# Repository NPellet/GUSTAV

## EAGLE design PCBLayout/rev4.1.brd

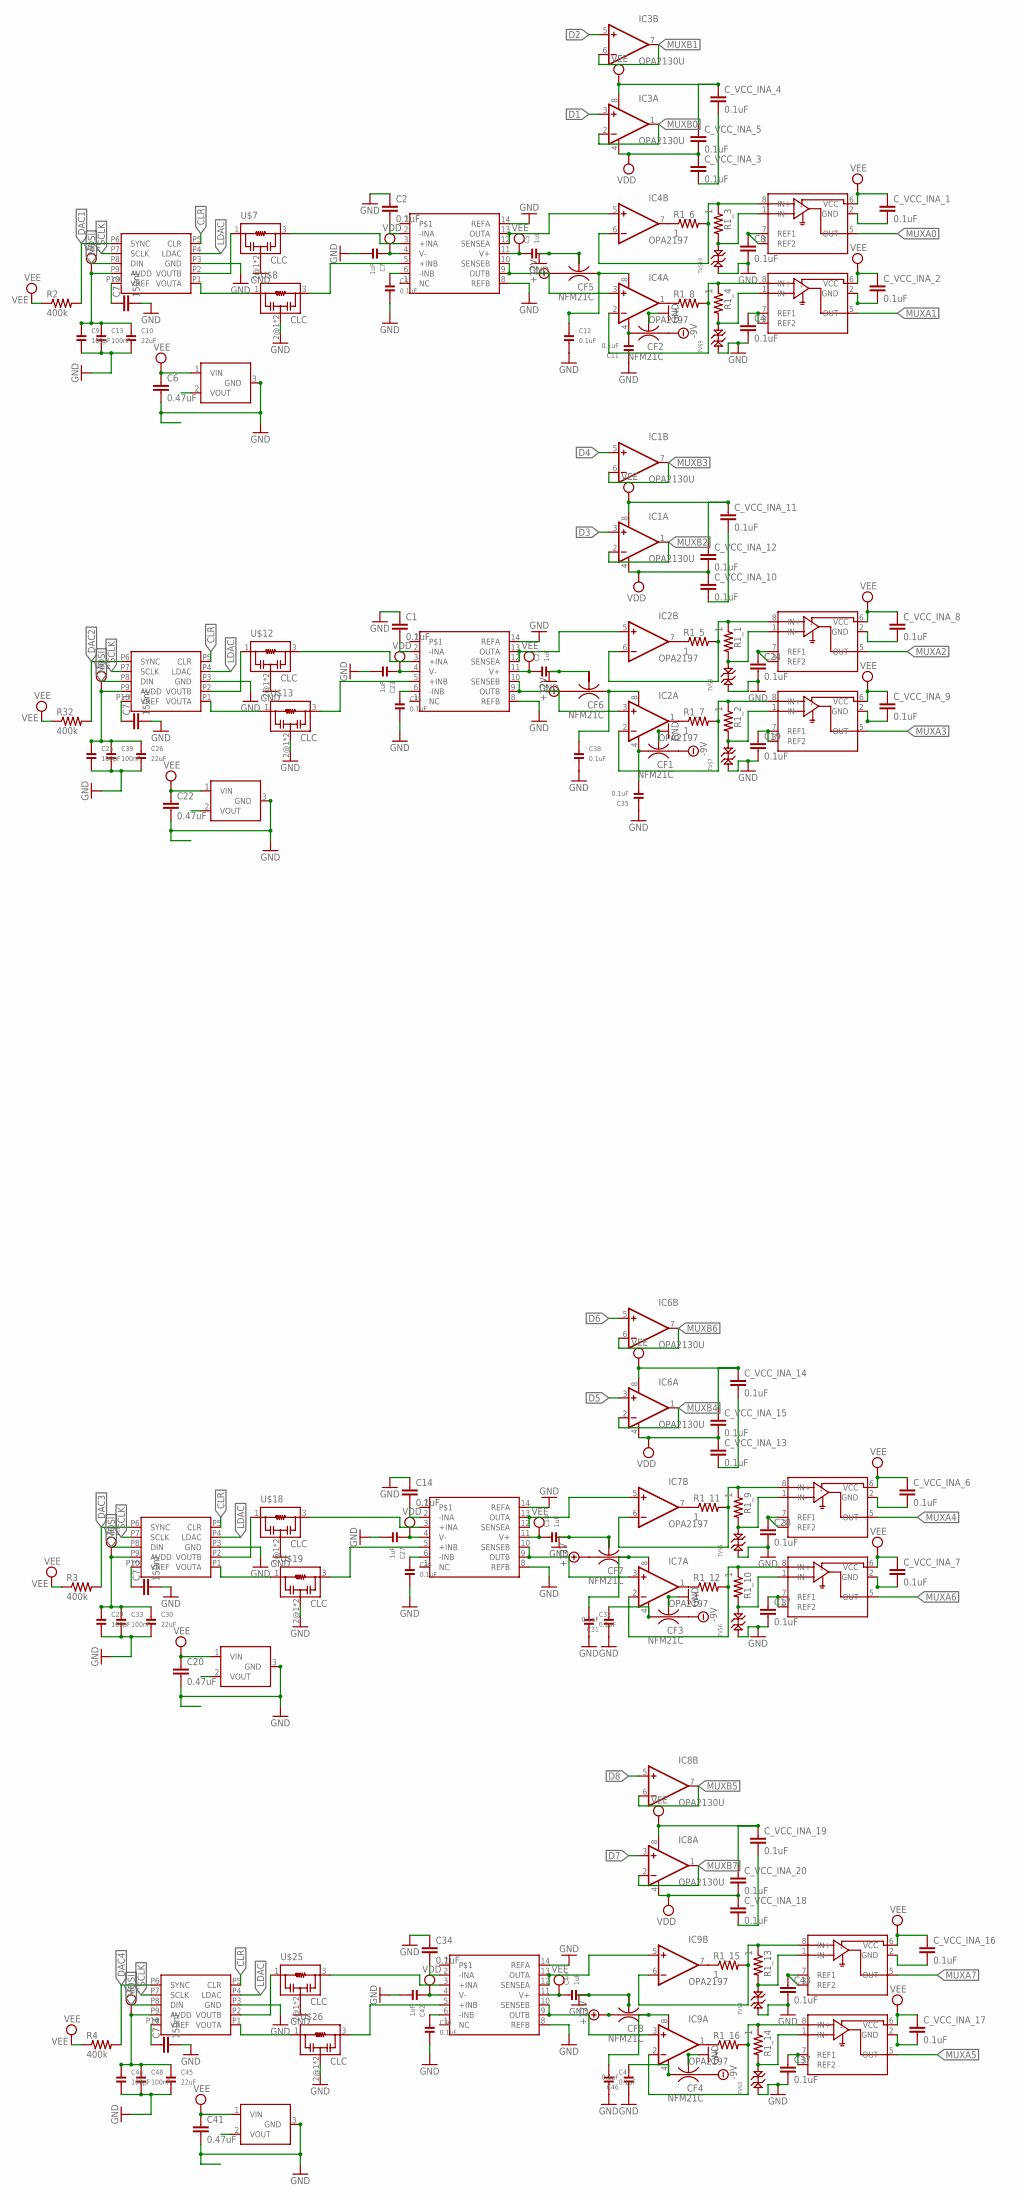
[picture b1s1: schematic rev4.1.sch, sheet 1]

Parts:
C1, C2, C4, C8, C14, C17, C19, C24, C28, C34, C37, C43: 0.1uF; 0402-CAP
C3, C11, C12, C15, C16, C31, C32, C35, C36, C38, C46, C47: 0.1uF; 0402
C5, C7, C18, C21, C23, C27, C40, C42: 1uF; 0402
C6, C20, C22, C41: 0.47uF; 0402-CAP
C7_1, C7_2, C7_3, C7_4: 150nF; 0402-CAP
C9, C25, C29, C44: 100pF; 0402
C10, C26, C30, C45: 22uF; 0805
C13, C33, C39, C48: 100nF; 0402
CF1, CF2, CF3, CF4, CF5, CF6, CF7, CF8: NFM21C
C_VCC_INA_1, C_VCC_INA_2, C_VCC_INA_3, C_VCC_INA_4, C_VCC_INA_5, C_VCC_INA_6, C_VCC_INA_7, C_VCC_INA_8, C_VCC_INA_9, C_VCC_INA_10, C_VCC_INA_11, C_VCC_INA_12, C_VCC_INA_13, C_VCC_INA_14, C_VCC_INA_15, C_VCC_INA_16, C_VCC_INA_17, C_VCC_INA_18, C_VCC_INA_19, C_VCC_INA_20: 0.1uF; 0402-CAP
IC1, IC3, IC6, IC8: OPA2130U; SO08
IC2, IC4, IC7, IC9: OPA2197; SO08
R1_1, R1_2, R1_3, R1_4, R1_5, R1_6, R1_7, R1_8, R1_9, R1_10, R1_11, R1_12, R1_13, R1_14, R1_15, R1_16: 1; 0603-RES
R2, R3, R4, R32: 400k; 0603-RES
REF1, REF2, REF3, REF4: REF3040; DBZ_R-PDSO-G3
TVS3, TVS4, TVS5, TVS6, TVS7, TVS8, TVS9, TVS10: TVS_DIODE_SOD-923; SOD-923
U$1, U$2, U$5, U$9, U$14, U$15, U$20, U$21: INA283; S-PDSO-G08-NOTHERMALPAD
U$3, U$10, U$16, U$23: INA2132; SO-14
U$4, U$11, U$17, U$24: DAC7563; S-PDSO-G10
U$7, U$8, U$12, U$13, U$18, U$19, U$25, U$26: CLC; NFM21C

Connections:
+12V: CF5.3, CF6.3, CF7.3, CF8.3; also elsewhere on the board
-9V: CF1.1, CF2.1, CF3.1, CF4.1; also elsewhere on the board
CLR: U$4.P5 (CLR), U$11.P5 (CLR), U$17.P5 (CLR), U$24.P5 (CLR); also elsewhere on the board
D1: IC3.3 (+IN), R1_3.2, TVS10.P$2, U$1.1 (IN-); also elsewhere on the board
D2: IC3.5 (+IN), R1_4.2, TVS9.P$2, U$2.1 (IN-); also elsewhere on the board
D3: IC1.3 (+IN), R1_1.2, TVS8.P$2, U$5.1 (IN-); also elsewhere on the board
D4: IC1.5 (+IN), R1_2.2, TVS7.P$2, U$9.1 (IN-); also elsewhere on the board
D5: IC6.3 (+IN), R1_9.2, TVS5.P$2, U$14.1 (IN-); also elsewhere on the board
D6: IC6.5 (+IN), R1_10.2, TVS6.P$2, U$15.1 (IN-); also elsewhere on the board
D7: IC8.3 (+IN), R1_13.2, TVS4.P$2, U$20.1 (IN-); also elsewhere on the board
D8: IC8.5 (+IN), R1_14.2, TVS3.P$2, U$21.1 (IN-); also elsewhere on the board
DAC1: R2.2, U$4.P6 (SYNC); also elsewhere on the board
DAC2: R32.2, U$11.P6 (SYNC); also elsewhere on the board
DAC3: R3.2, U$17.P6 (SYNC); also elsewhere on the board
DAC4: R4.2, U$24.P6 (SYNC); also elsewhere on the board
DACOUTA1: U$4.P1 (VOUTA), U$8.1
DACOUTA2: U$11.P1 (VOUTA), U$13.1
DACOUTA3: U$17.P1 (VOUTA), U$19.1
DACOUTA4: U$24.P1 (VOUTA), U$26.1
DACOUTAFIL1: U$3.5 (+INB), U$8.3
DACOUTAFIL2: U$10.5 (+INB), U$13.3
DACOUTAFIL3: U$16.5 (+INB), U$19.3
DACOUTAFIL4: U$23.5 (+INB), U$26.3
DACOUTB1: U$4.P2 (VOUTB), U$7.1
DACOUTB2: U$11.P2 (VOUTB), U$12.1
DACOUTB3: U$17.P2 (VOUTB), U$18.1
DACOUTB4: U$24.P2 (VOUTB), U$25.1
DACOUTBFIL1: U$3.3 (+INA), U$7.3
DACOUTBFIL2: U$10.3 (+INA), U$12.3
DACOUTBFIL3: U$16.3 (+INA), U$18.3
DACOUTBFIL4: U$23.3 (+INA), U$25.3
GND: C1.1, C2.1, C3.2, C4.2, C5.2, C6.2, C7.2, C7_1.2, C7_2.2, C7_3.2, C7_4.2, C8.2, C9.2, C10.2, C11.1, C12.2, C13.2, C14.1, C15.2, C16.2, C17.2, C18.2, C19.2, C20.2, C21.2, C22.2, C23.2, C24.2, C25.2, C26.2, C27.2, C28.2, C29.2, C30.2, C31.1, C32.2, C33.2, C34.1, C35.1, C36.2, C37.2, C38.2, C39.2, C40.2, C41.2, C42.2, C43.2, C44.2, C45.2, C46.1, C47.2, C48.2, CF1.2@1 (2), CF1.2@2 (2), CF2.2@1 (2), CF2.2@2 (2), CF3.2@1 (2), CF3.2@2 (2), CF4.2@1 (2), CF4.2@2 (2), CF5.2@1 (2), CF5.2@2 (2), CF6.2@1 (2), CF7.2@1 (2), CF7.2@2 (2), CF8.2@1 (2), CF8.2@2 (2), C_VCC_INA_1.2, C_VCC_INA_2.2, C_VCC_INA_3.2, C_VCC_INA_4.2, C_VCC_INA_6.2, C_VCC_INA_7.2, C_VCC_INA_8.2, C_VCC_INA_9.2, C_VCC_INA_10.2, C_VCC_INA_11.2, C_VCC_INA_13.2, C_VCC_INA_14.2, C_VCC_INA_16.2, C_VCC_INA_17.2, C_VCC_INA_18.2, C_VCC_INA_19.2, REF1.3 (GND), REF2.3 (GND), REF3.3 (GND), REF4.3 (GND), TVS3.P$1, TVS4.P$1, TVS5.P$1, TVS6.P$1, TVS7.P$1, TVS8.P$1, TVS9.P$1, TVS10.P$1, U$1.2 (GND), U$2.2 (GND), U$3.8 (REFB), U$3.14 (REFA), U$4.P3 (GND), U$5.2 (GND), U$7.2@1 (2), U$7.2@2 (2), U$8.2@1 (2), U$8.2@2 (2), U$9.2 (GND), U$10.8 (REFB), U$10.14 (REFA), U$11.P3 (GND), U$12.2@1 (2), U$12.2@2 (2), U$13.2@1 (2), U$13.2@2 (2), U$14.2 (GND), U$15.2 (GND), U$16.8 (REFB), U$16.14 (REFA), U$17.P3 (GND), U$18.2@1 (2), U$18.2@2 (2), U$19.2@1 (2), U$19.2@2 (2), U$20.2 (GND), U$21.2 (GND), U$23.8 (REFB), U$23.14 (REFA), U$24.P3 (GND), U$25.2@1 (2), U$25.2@2 (2), U$26.2@1 (2), U$26.2@2 (2); also elsewhere on the board
LDAC: U$4.P4 (LDAC), U$11.P4 (LDAC), U$17.P4 (LDAC), U$24.P4 (LDAC); also elsewhere on the board
MOSI: U$4.P8 (DIN), U$11.P8 (DIN), U$17.P8 (DIN), U$24.P8 (DIN); also elsewhere on the board
MUXA0: U$1.5 (OUT); also elsewhere on the board
MUXA1: U$2.5 (OUT); also elsewhere on the board
MUXA2: U$5.5 (OUT); also elsewhere on the board
MUXA3: U$9.5 (OUT); also elsewhere on the board
MUXA4: U$14.5 (OUT); also elsewhere on the board
MUXA5: U$21.5 (OUT); also elsewhere on the board
MUXA6: U$15.5 (OUT); also elsewhere on the board
MUXA7: U$20.5 (OUT); also elsewhere on the board
MUXB0: IC3.1 (OUT), IC3.2 (-IN); also elsewhere on the board
MUXB1: IC3.6 (-IN), IC3.7 (OUT); also elsewhere on the board
MUXB2: IC1.1 (OUT), IC1.2 (-IN); also elsewhere on the board
MUXB3: IC1.6 (-IN), IC1.7 (OUT); also elsewhere on the board
MUXB4: IC6.1 (OUT), IC6.2 (-IN); also elsewhere on the board
MUXB5: IC8.6 (-IN), IC8.7 (OUT); also elsewhere on the board
MUXB6: IC6.6 (-IN), IC6.7 (OUT); also elsewhere on the board
MUXB7: IC8.1 (OUT), IC8.2 (-IN); also elsewhere on the board
unnamed: IC2.5 (+IN), U$10.12 (SENSEA), U$10.13 (OUTA)
unnamed: IC4.5 (+IN), U$3.12 (SENSEA), U$3.13 (OUTA)
unnamed: IC4.3 (+IN), U$3.9 (OUTB), U$3.10 (SENSEB)
unnamed: IC2.7 (OUT), R1_5.1
unnamed: IC4.7 (OUT), R1_6.1
unnamed: IC4.2 (-IN), R1_4.1, R1_8.2, U$2.8 (IN+)
unnamed: IC2.2 (-IN), R1_2.1, R1_7.2, U$9.8 (IN+)
unnamed: IC2.1 (OUT), R1_7.1
unnamed: IC4.1 (OUT), R1_8.1
unnamed: IC2.3 (+IN), U$10.9 (OUTB), U$10.10 (SENSEB)
unnamed: IC7.5 (+IN), U$16.12 (SENSEA), U$16.13 (OUTA)
unnamed: IC7.3 (+IN), U$16.9 (OUTB), U$16.10 (SENSEB)
unnamed: IC7.7 (OUT), R1_11.1
unnamed: IC7.2 (-IN), R1_10.1, R1_12.2, U$15.8 (IN+)
unnamed: IC7.1 (OUT), R1_12.1
unnamed: IC9.5 (+IN), U$23.12 (SENSEA), U$23.13 (OUTA)
unnamed: IC9.3 (+IN), U$23.9 (OUTB), U$23.10 (SENSEB)
unnamed: IC9.7 (OUT), R1_15.1
unnamed: IC9.2 (-IN), R1_14.1, R1_16.2, U$21.8 (IN+)
unnamed: IC9.1 (OUT), R1_16.1
unnamed: C11.2, CF2.3, IC4.4 (V-)
unnamed: C38.1, CF6.1, IC2.8 (V+)
unnamed: C35.2, CF1.3, IC2.4 (V-)
unnamed: C31.2, CF3.3, IC7.4 (V-)
unnamed: C46.2, CF4.3, IC9.4 (V-)
unnamed: C12.1, CF5.1, IC4.8 (V+)
unnamed: C47.1, CF8.1, IC9.8 (V+)
unnamed: C32.1, CF7.1, IC7.8 (V+)
OUT1: IC4.6 (-IN), R1_3.1, R1_6.2, U$1.8 (IN+)
OUT2: IC7.6 (-IN), R1_9.1, R1_11.2, U$14.8 (IN+)
OUT3: IC9.6 (-IN), R1_13.1, R1_15.2, U$20.8 (IN+)
OUT4: IC2.6 (-IN), R1_1.1, R1_5.2, U$5.8 (IN+)
REF2: C1.2, C2.2, C3.1, C4.1, C8.1, C14.2, C15.1, C16.1, C17.1, C19.1, C24.1, C28.1, C34.2, C36.1, C37.1, C43.1, U$1.3 (REF2), U$1.7 (REF1), U$2.3 (REF2), U$2.7 (REF1), U$3.2 (-INA), U$3.6 (-INB), U$5.3 (REF2), U$5.7 (REF1), U$9.3 (REF2), U$9.7 (REF1), U$10.2 (-INA), U$10.6 (-INB), U$14.3 (REF2), U$14.7 (REF1), U$15.3 (REF2), U$15.7 (REF1), U$16.2 (-INA), U$16.6 (-INB), U$20.3 (REF2), U$20.7 (REF1), U$21.3 (REF2), U$21.7 (REF1), U$23.2 (-INA), U$23.6 (-INB); also elsewhere on the board
REF3: C7_1.1, REF1.2 (VOUT), U$11.P10 (VREF)
REF4: C7_2.1, REF2.2 (VOUT), U$4.P10 (VREF)
REF6: C7_3.1, REF3.2 (VOUT), U$17.P10 (VREF)
REF8: C7_4.1, REF4.2 (VOUT), U$24.P10 (VREF)
SCLK: U$4.P7 (SCLK), U$11.P7 (SCLK), U$17.P7 (SCLK), U$24.P7 (SCLK); also elsewhere on the board
VDD: C7.1, C23.1, C27.1, C42.1, C_VCC_INA_3.1, C_VCC_INA_5.2, C_VCC_INA_10.1, C_VCC_INA_12.2, C_VCC_INA_13.1, C_VCC_INA_15.2, C_VCC_INA_18.1, C_VCC_INA_20.2, IC1.4 (V-), IC3.4 (V-), IC6.4 (V-), IC8.4 (V-), U$3.4 (V-), U$10.4 (V-), U$16.4 (V-), U$23.4 (V-); also elsewhere on the board
VEE: C5.1, C6.1, C9.1, C10.1, C13.1, C18.1, C20.1, C21.1, C22.1, C25.1, C26.1, C29.1, C30.1, C33.1, C39.1, C40.1, C41.1, C44.1, C45.1, C48.1, C_VCC_INA_1.1, C_VCC_INA_2.1, C_VCC_INA_4.1, C_VCC_INA_5.1, C_VCC_INA_6.1, C_VCC_INA_7.1, C_VCC_INA_8.1, C_VCC_INA_9.1, C_VCC_INA_11.1, C_VCC_INA_12.1, C_VCC_INA_14.1, C_VCC_INA_15.1, C_VCC_INA_16.1, C_VCC_INA_17.1, C_VCC_INA_19.1, C_VCC_INA_20.1, IC1.8 (V+), IC3.8 (V+), IC6.8 (V+), IC8.8 (V+), R2.1, R3.1, R4.1, R32.1, REF1.1 (VIN), REF2.1 (VIN), REF3.1 (VIN), REF4.1 (VIN), U$1.6 (VCC), U$2.6 (VCC), U$3.11 (V+), U$4.P9 (AVDD), U$5.6 (VCC), U$9.6 (VCC), U$10.11 (V+), U$11.P9 (AVDD), U$14.6 (VCC), U$15.6 (VCC), U$16.11 (V+), U$17.P9 (AVDD), U$20.6 (VCC), U$21.6 (VCC), U$23.11 (V+), U$24.P9 (AVDD); also elsewhere on the board

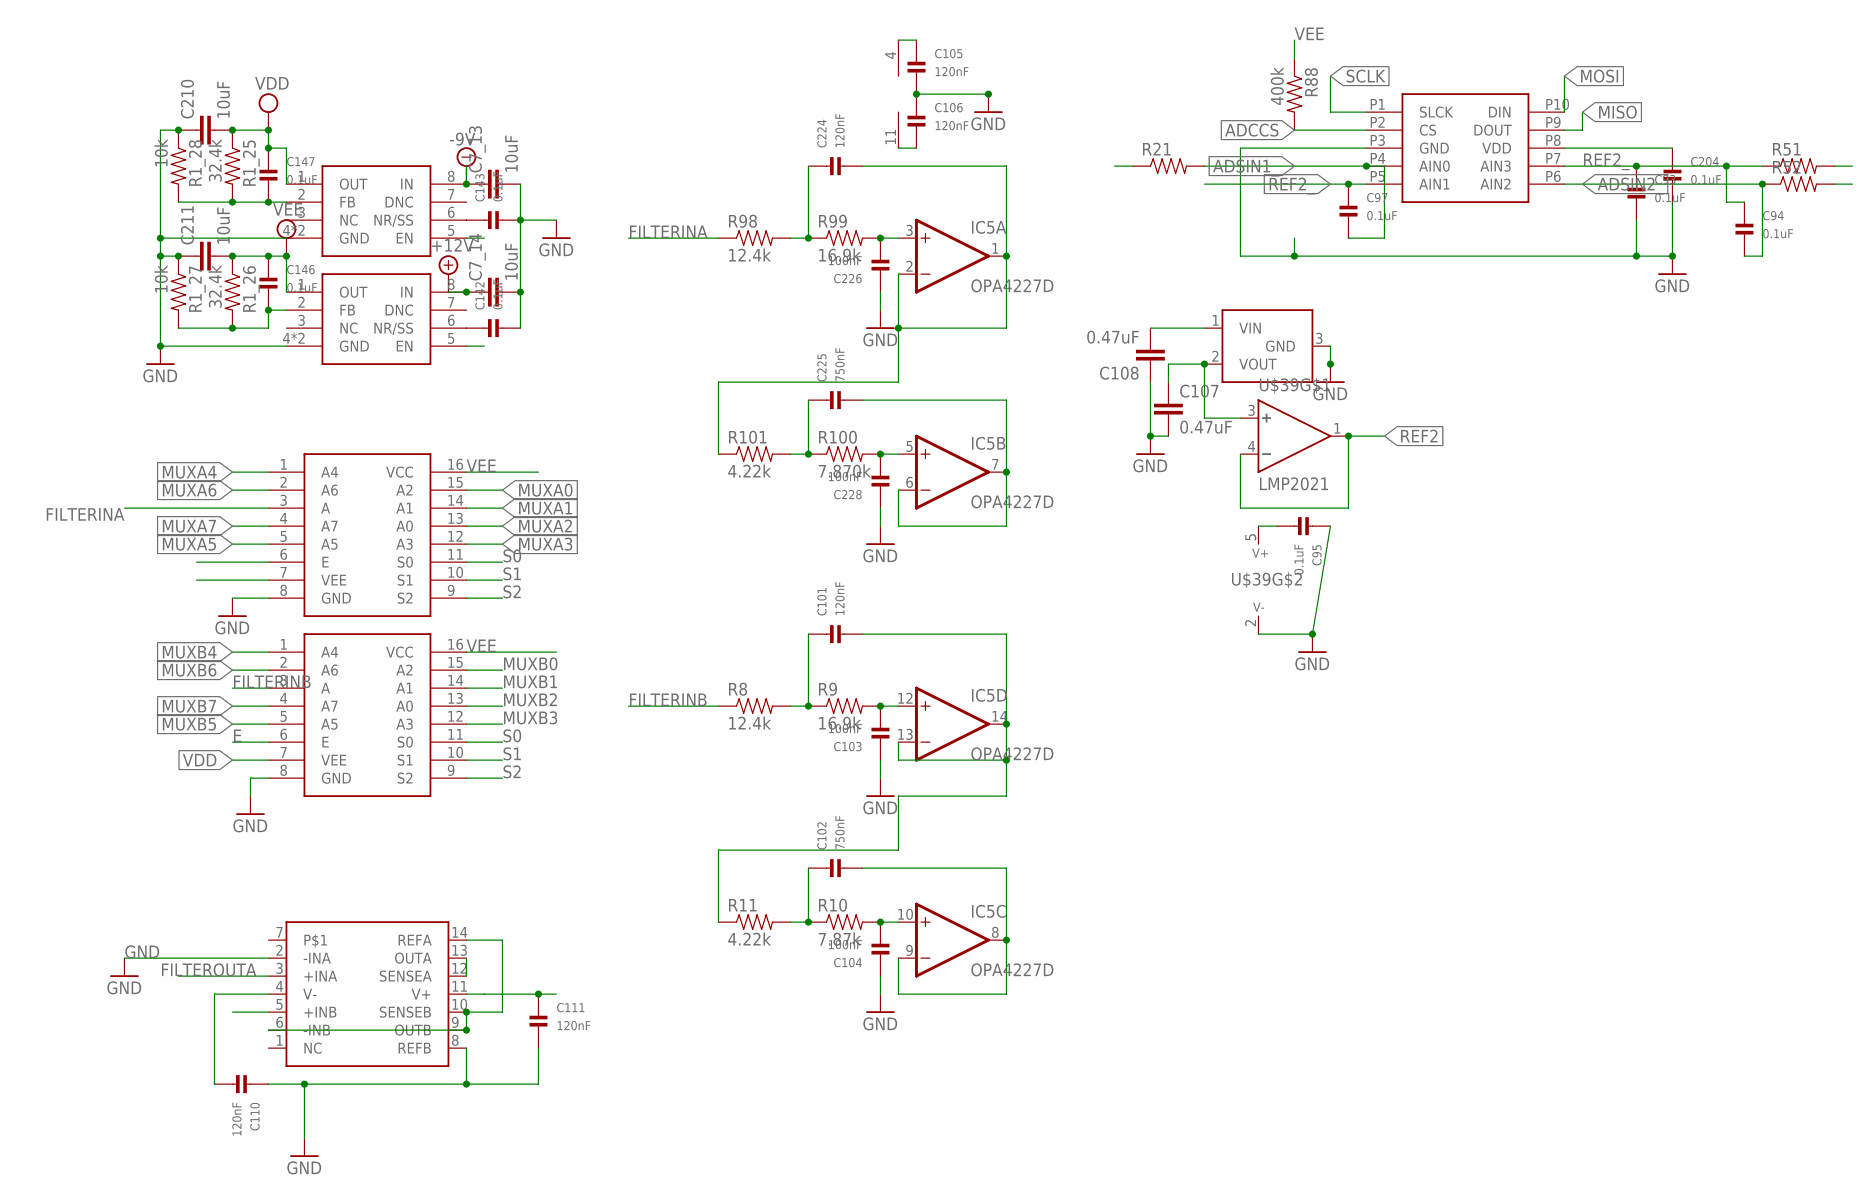
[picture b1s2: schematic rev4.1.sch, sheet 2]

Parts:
C7_13, C7_14, C210, C211: 10uF; 0805
C93, C94, C95, C97, C142, C143, C146, C147, C204: 0.1uF; 0402
C101, C105, C106, C110, C111, C224: 120nF; 0402
C102, C225: 750nF; 0402
C103, C104, C226, C228: 100nF; 0402
C107, C108: 0.47uF; 0402-CAP
IC5: OPA4227D; SO14
R1_25, R1_26: 32.4k; 0603-RES
R1_27, R1_28: 10k; 0603-RES
R8, R98: 12.4k; 0603-RES
R9, R99: 16.9k; 0603-RES
R10: 7.87k; 0603-RES
R11, R101: 4.22k; 0603-RES
R21, R51, R52: RESISTOR0603-RES; 0603-RES
R88: 400k; 0603-RES
R100: 7.870k; 0603-RES
REF7: REF3020; DBZ_R-PDSO-G3
U$6, U$57: CD54HC4051; PW_R-PDSO-G16
U$39: LMP2021; SOT23-DBV
U$40: ADS1018; S-PDSO-G10
U$48, U$49: TPS7A30; S-PDSO-G08
U$58: INA2132; SO-14

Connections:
+12V: C7_14.1, U$49.8 (IN); also elsewhere on the board
-9V: C7_13.1, U$48.8 (IN); also elsewhere on the board
ADCCS: R88.2, U$40.P2 (CS); also elsewhere on the board
ADSIN1: C102.2, IC5.8 (OUT), IC5.9 (-IN), R21.1
ADSIN1_: C97.2, R21.2, U$40.P4 (AIN0)
ADSIN2: R52.2, U$58.12 (SENSEA), U$58.13 (OUTA)
ADSIN2_: C94.2, R52.1, U$40.P6 (AIN2)
E: U$6.6 (E), U$57.6 (E); also elsewhere on the board
EN: U$48.5 (EN), U$49.5 (EN); also elsewhere on the board
FILTERINA: R98.1, U$6.3 (A)
FILTERINB: R8.1, U$57.3 (A)
FILTEROUTA: C225.2, IC5.6 (-IN), IC5.7 (OUT), U$58.3 (+INA)
GND: C7_13.2, C7_14.2, C93.2, C95.1, C103.1, C104.1, C105.2, C106.1, C107.2, C108.1, C110.1, C111.2, C142.2, C143.2, C204.2, C210.1, C211.1, C226.1, C228.1, R1_27.1, R1_28.1, REF7.3 (GND), U$6.8 (GND), U$39.2 (V-), U$40.P3 (GND), U$48.4 (GND), U$48.TH (GND), U$49.4 (GND), U$49.TH (GND), U$57.8 (GND), U$58.2 (-INA), U$58.8 (REFB); also elsewhere on the board
MISO: U$40.P9 (DOUT); also elsewhere on the board
MOSI: U$40.P10 (DIN); also elsewhere on the board
MUXA0: U$6.15 (A2); also elsewhere on the board
MUXA1: U$6.14 (A1); also elsewhere on the board
MUXA2: U$6.13 (A0); also elsewhere on the board
MUXA3: U$6.12 (A3); also elsewhere on the board
MUXA4: U$6.1 (A4); also elsewhere on the board
MUXA5: U$6.5 (A5); also elsewhere on the board
MUXA6: U$6.2 (A6); also elsewhere on the board
MUXA7: U$6.4 (A7); also elsewhere on the board
MUXB0: U$57.15 (A2); also elsewhere on the board
MUXB1: U$57.14 (A1); also elsewhere on the board
MUXB2: U$57.13 (A0); also elsewhere on the board
MUXB3: U$57.12 (A3); also elsewhere on the board
MUXB4: U$57.1 (A4); also elsewhere on the board
MUXB5: U$57.5 (A5); also elsewhere on the board
MUXB6: U$57.2 (A6); also elsewhere on the board
MUXB7: U$57.4 (A7); also elsewhere on the board
unnamed: C107.1, REF7.2 (VOUT), U$39.3 (+)
unnamed: C101.2, IC5.13 (-IN), IC5.14 (OUT), R11.1
unnamed: C103.2, IC5.12 (+IN), R9.2
unnamed: C104.2, IC5.10 (+IN), R10.2
unnamed: C102.1, R10.1, R11.2
unnamed: U$58.6 (-INB), U$58.9 (OUTB), U$58.10 (SENSEB), U$58.14 (REFA)
unnamed: C101.1, R8.2, R9.1
unnamed: C143.1, U$48.6 (NR/SS)
unnamed: C142.1, U$49.6 (NR/SS)
unnamed: C146.2, R1_26.2, R1_27.2, U$49.2 (FB)
unnamed: C147.2, R1_25.2, R1_28.2, U$48.2 (FB)
unnamed: C226.2, IC5.3 (+IN), R99.2
unnamed: C228.2, IC5.5 (+IN), R100.2
unnamed: C225.1, R100.1, R101.2
unnamed: C224.2, IC5.1 (OUT), IC5.2 (-IN), R101.1
unnamed: C224.1, R98.2, R99.1
REF2: R51.2, U$39.1 (OUT), U$39.4 (-), U$58.5 (+INB); also elsewhere on the board
REF2_: C93.1, C94.1, C97.1, R51.1, U$40.P5 (AIN1), U$40.P7 (AIN3)
S0: U$6.11 (S0), U$57.11 (S0); also elsewhere on the board
S1: U$6.10 (S1), U$57.10 (S1); also elsewhere on the board
S2: U$6.9 (S2), U$57.9 (S2); also elsewhere on the board
SCLK: U$40.P1 (SLCK); also elsewhere on the board
VDD: C106.2, C111.1, C147.1, C210.2, IC5.11 (V-), R1_25.1, U$6.7 (VEE), U$48.1 (OUT), U$57.7 (VEE), U$58.11 (V+); also elsewhere on the board
VEE: C95.2, C105.1, C108.2, C110.2, C146.1, C204.1, C211.2, IC5.4 (V+), R1_26.1, R88.1, REF7.1 (VIN), U$6.16 (VCC), U$39.5 (V+), U$40.P8 (VDD), U$49.1 (OUT), U$57.16 (VCC), U$58.4 (V-); also elsewhere on the board

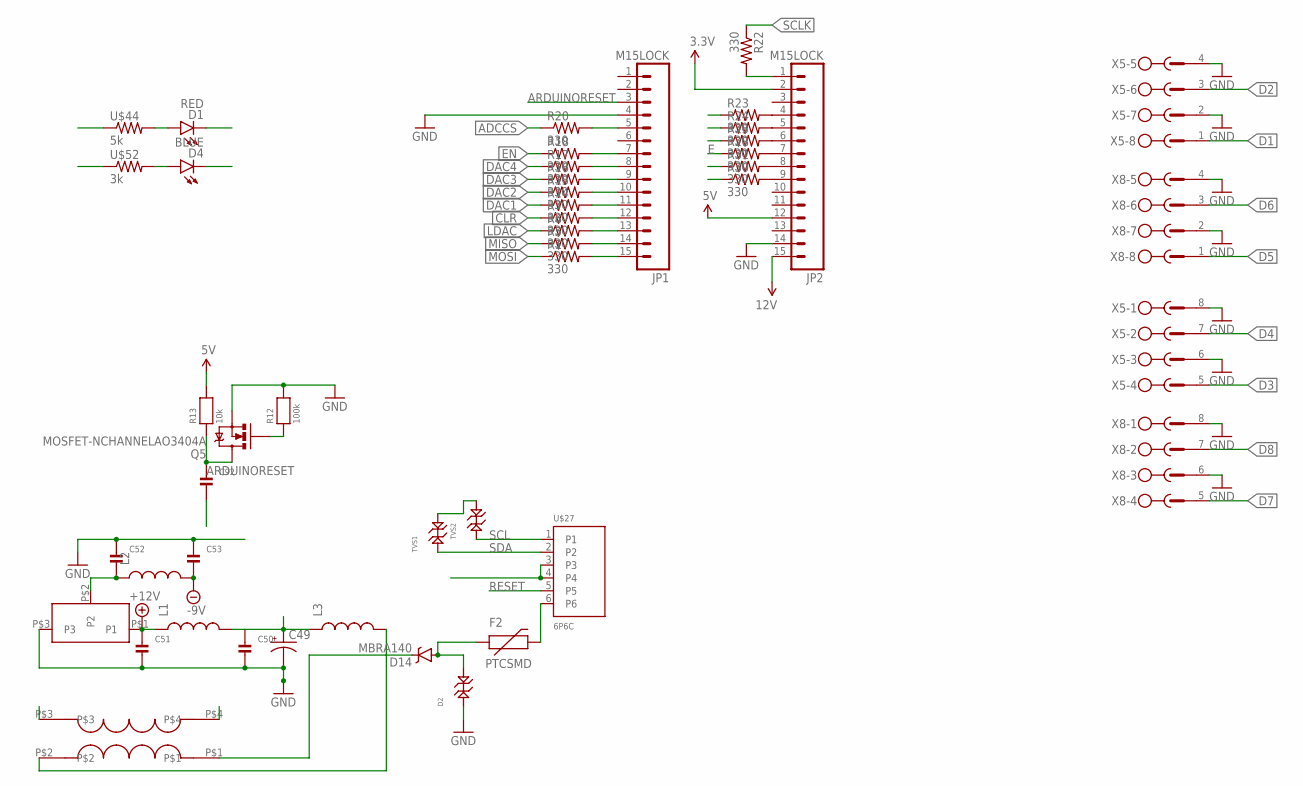
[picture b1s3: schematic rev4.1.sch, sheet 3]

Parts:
C49: CAP_POLH13; PANASONIC_H13
C50, C51, C52, C53: CAP_CERAMIC1206; 1206
C92: CAP_CERAMIC0402; 0402
D1: RED; LED-1206
D2: TVS_DIODE_SOD-923; SOD-923
D4: BLUE; LED-1206
D14: MBRA140; SMA-DIODE
F2: PTCSMD; PTC-1206
JP1, JP2: M15LOCK; 1X15_LOCK
L1, L2, L3: INDUCTORINDUCTOR_12MM_BOURNS; INDUCTOR-12MM_BOURNS
Q5: MOSFET-NCHANNELAO3404A; SOT23-3
R1, R5, R6, R7, R14, R15, R16, R17, R18, R20, R22, R23, R24, R25, R28, R30, R31: 330; 0603-RES
R12: 100k; 0402
R13: 10k; 0402
TVS1, TVS2: TVS_DIODE_SOD-923; SOD-923
U$22: COMMONMODEFILTER2014; 2014
U$27: 6P6C
U$42: TSRN1
U$44: 5k; 0603
U$52: 3k; 0603
X5, X8: MSTBV8

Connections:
3.3V: JP2.2
5V: JP2.12, R13.2
+12V: C51.1, JP2.15, L1.P$1 (1), U$42.P$1 (P1), U$44.1; also elsewhere on the board
-9V: C53.2, D4.C, L2.P$2 (2); also elsewhere on the board
ADCCS: R20.1; also elsewhere on the board
ARDUINORESET: C92.1, JP1.3, Q5.3 (D), R13.1
CLR: R7.1; also elsewhere on the board
D1: X5.1; also elsewhere on the board
D2: X5.3; also elsewhere on the board
D3: X5.5; also elsewhere on the board
D4: X5.7; also elsewhere on the board
D5: X8.1; also elsewhere on the board
D6: X8.3; also elsewhere on the board
D7: X8.5; also elsewhere on the board
D8: X8.7; also elsewhere on the board
D13: JP1.15, R1.2
D14: JP1.14, R5.2
D15: JP1.13, R6.2
D16: JP1.12, R7.2
D17: JP1.11, R14.2
D18: JP1.10, R15.2
D19: JP1.9, R16.2
D20: JP1.8, R17.2
D21: JP1.7, R18.2
D23: JP1.5, R20.2
DAC1: R14.1; also elsewhere on the board
DAC2: R15.1; also elsewhere on the board
DAC3: R16.1; also elsewhere on the board
DAC4: R17.1; also elsewhere on the board
E: R28.1; also elsewhere on the board
EN: R18.1; also elsewhere on the board
GND: C49.-, C50.2, C51.2, C52.1, C53.1, C92.2, D1.C, D2.P$1, JP1.4, JP2.14, Q5.2 (S), R12.2, TVS1.P$2, TVS2.P$2, U$22.P$3, U$42.P$3 (P3), U$52.1, X5.2, X5.4, X5.6, X5.8, X8.2, X8.4, X8.6, X8.8; also elsewhere on the board
LDAC: R6.1; also elsewhere on the board
MISO: R5.1; also elsewhere on the board
MOSI: R1.1; also elsewhere on the board
unnamed: JP2.7, R28.2
unnamed: JP2.9, R30.2
unnamed: JP2.1, R22.2
unnamed: JP2.8, R31.2
unnamed: JP2.4, R23.2
unnamed: D1.A, U$44.2
unnamed: JP2.5, R24.2
unnamed: JP2.6, R25.2
unnamed: C49.+, C50.1, L1.P$2 (2), L3.P$1 (1)
unnamed: C52.2, L2.P$1 (1), U$42.P$2 (P2)
unnamed: L3.P$2 (2), U$22.P$2
unnamed: D14.C, U$22.P$1
unnamed: F2.2, U$27.6
unnamed: D4.A, U$52.2
POW-: U$22.P$4, U$27.3, U$27.4
RESET: Q5.1 (G), R12.1, U$27.5
S0: R23.1; also elsewhere on the board
S1: R24.1; also elsewhere on the board
S2: R25.1; also elsewhere on the board
SCL: R30.1, TVS2.P$1, U$27.1
SCLK: R22.1; also elsewhere on the board
SDA: R31.1, TVS1.P$1, U$27.2
VPOS: D2.P$2, D14.A, F2.1

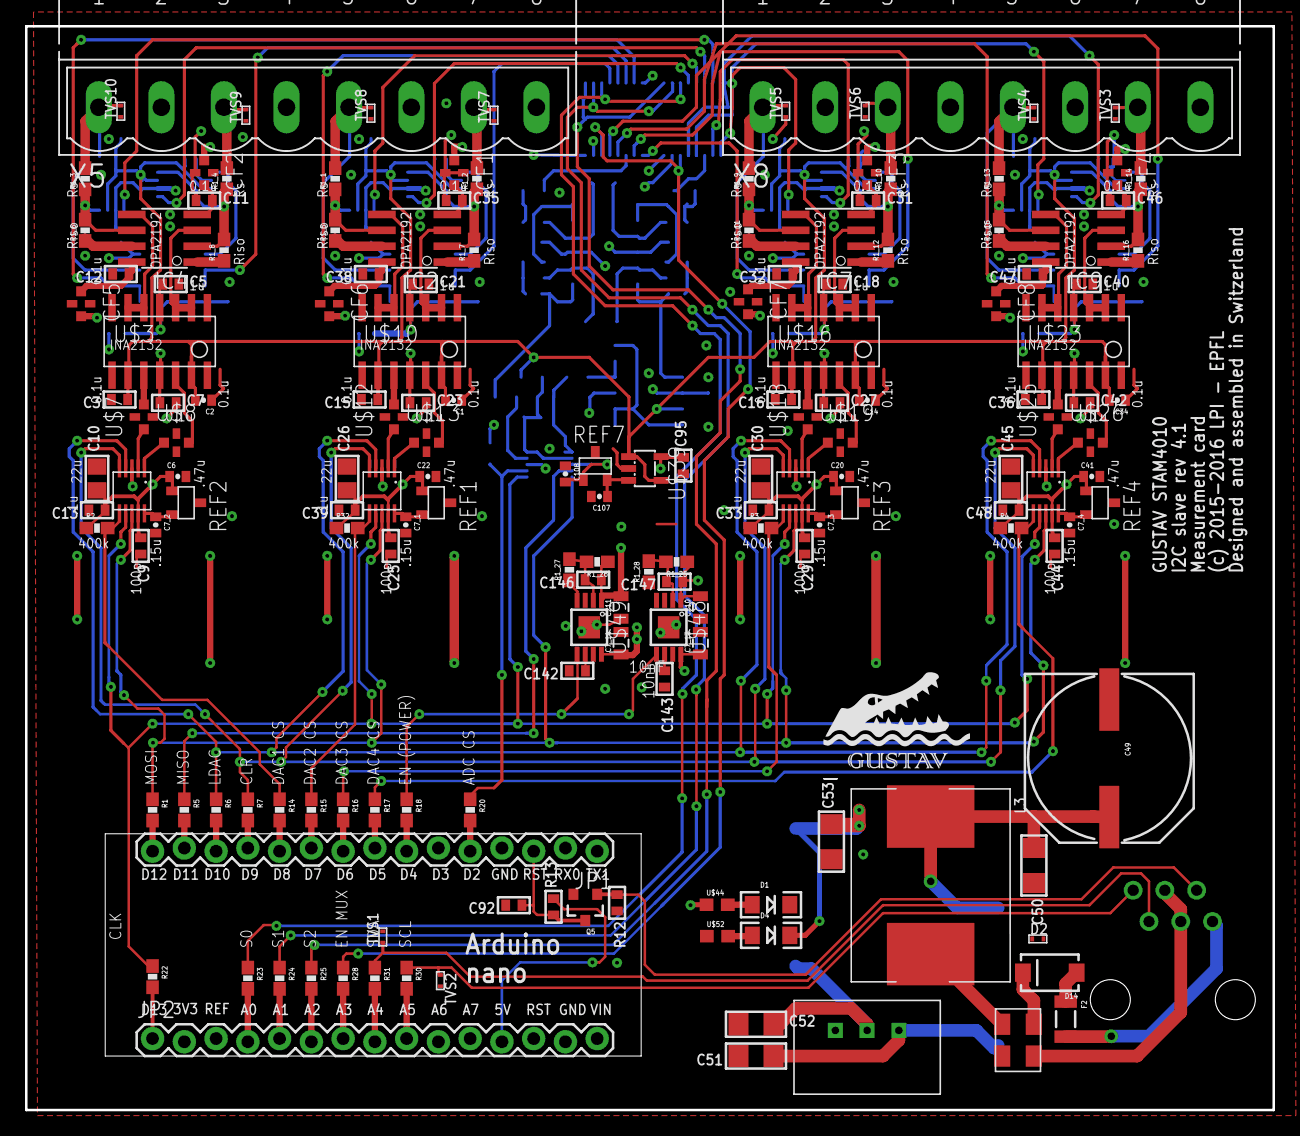
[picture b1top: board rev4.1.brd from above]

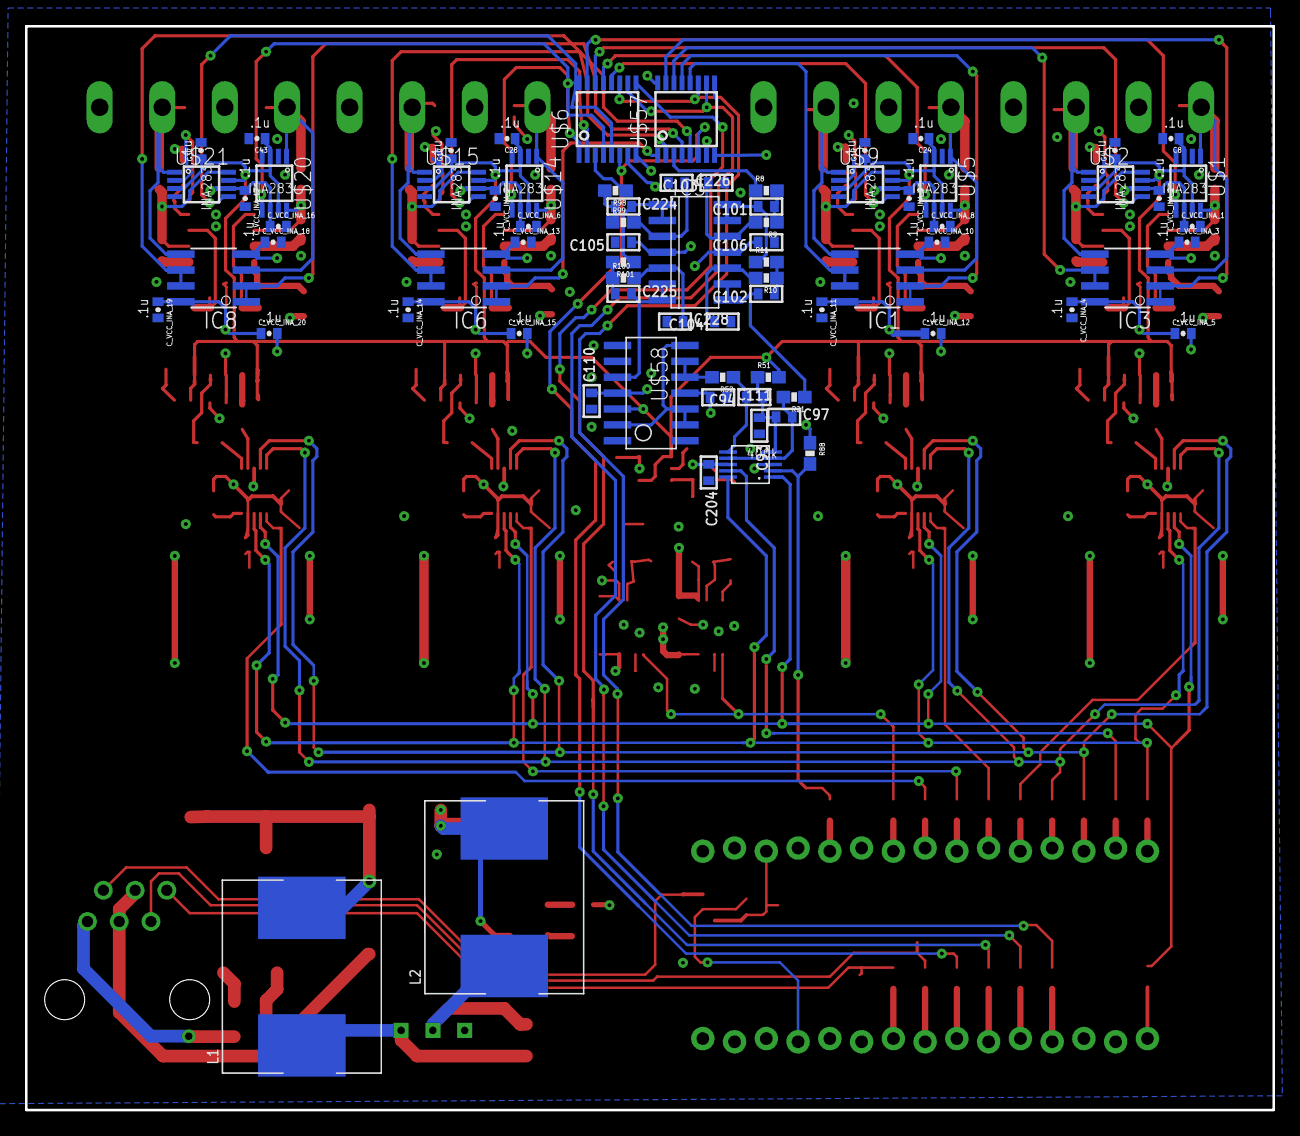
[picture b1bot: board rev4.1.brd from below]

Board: 4 copper layers, 99.8 x 86.7 mm, 242 parts (75 on the bottom side), 152 nets.

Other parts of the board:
U$41: LOGO_TEXT

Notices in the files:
PCBLayout/rev4.0.brd:
(c) 2015-2016 LPI - EPFL, Norman Pellet
parts and their libraries:
SparkFun-Capacitors: Licensing: Creative Commons ShareAlike 4.0 International - https://creativecommons.org/licenses/by-sa/4.0
microbuilder: This work is placed in the public domain, and may be freely used for commercial and non-commercial work with the following conditions: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
